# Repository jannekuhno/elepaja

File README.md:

# elepaja

#Setup
##1. Download KiCad
### Win:
http://kicad-pcb.org/ and install
### Linux:
sudo apt install kicad
##2. Clone repo
##3. Open project in KiCad
##4. Profit.

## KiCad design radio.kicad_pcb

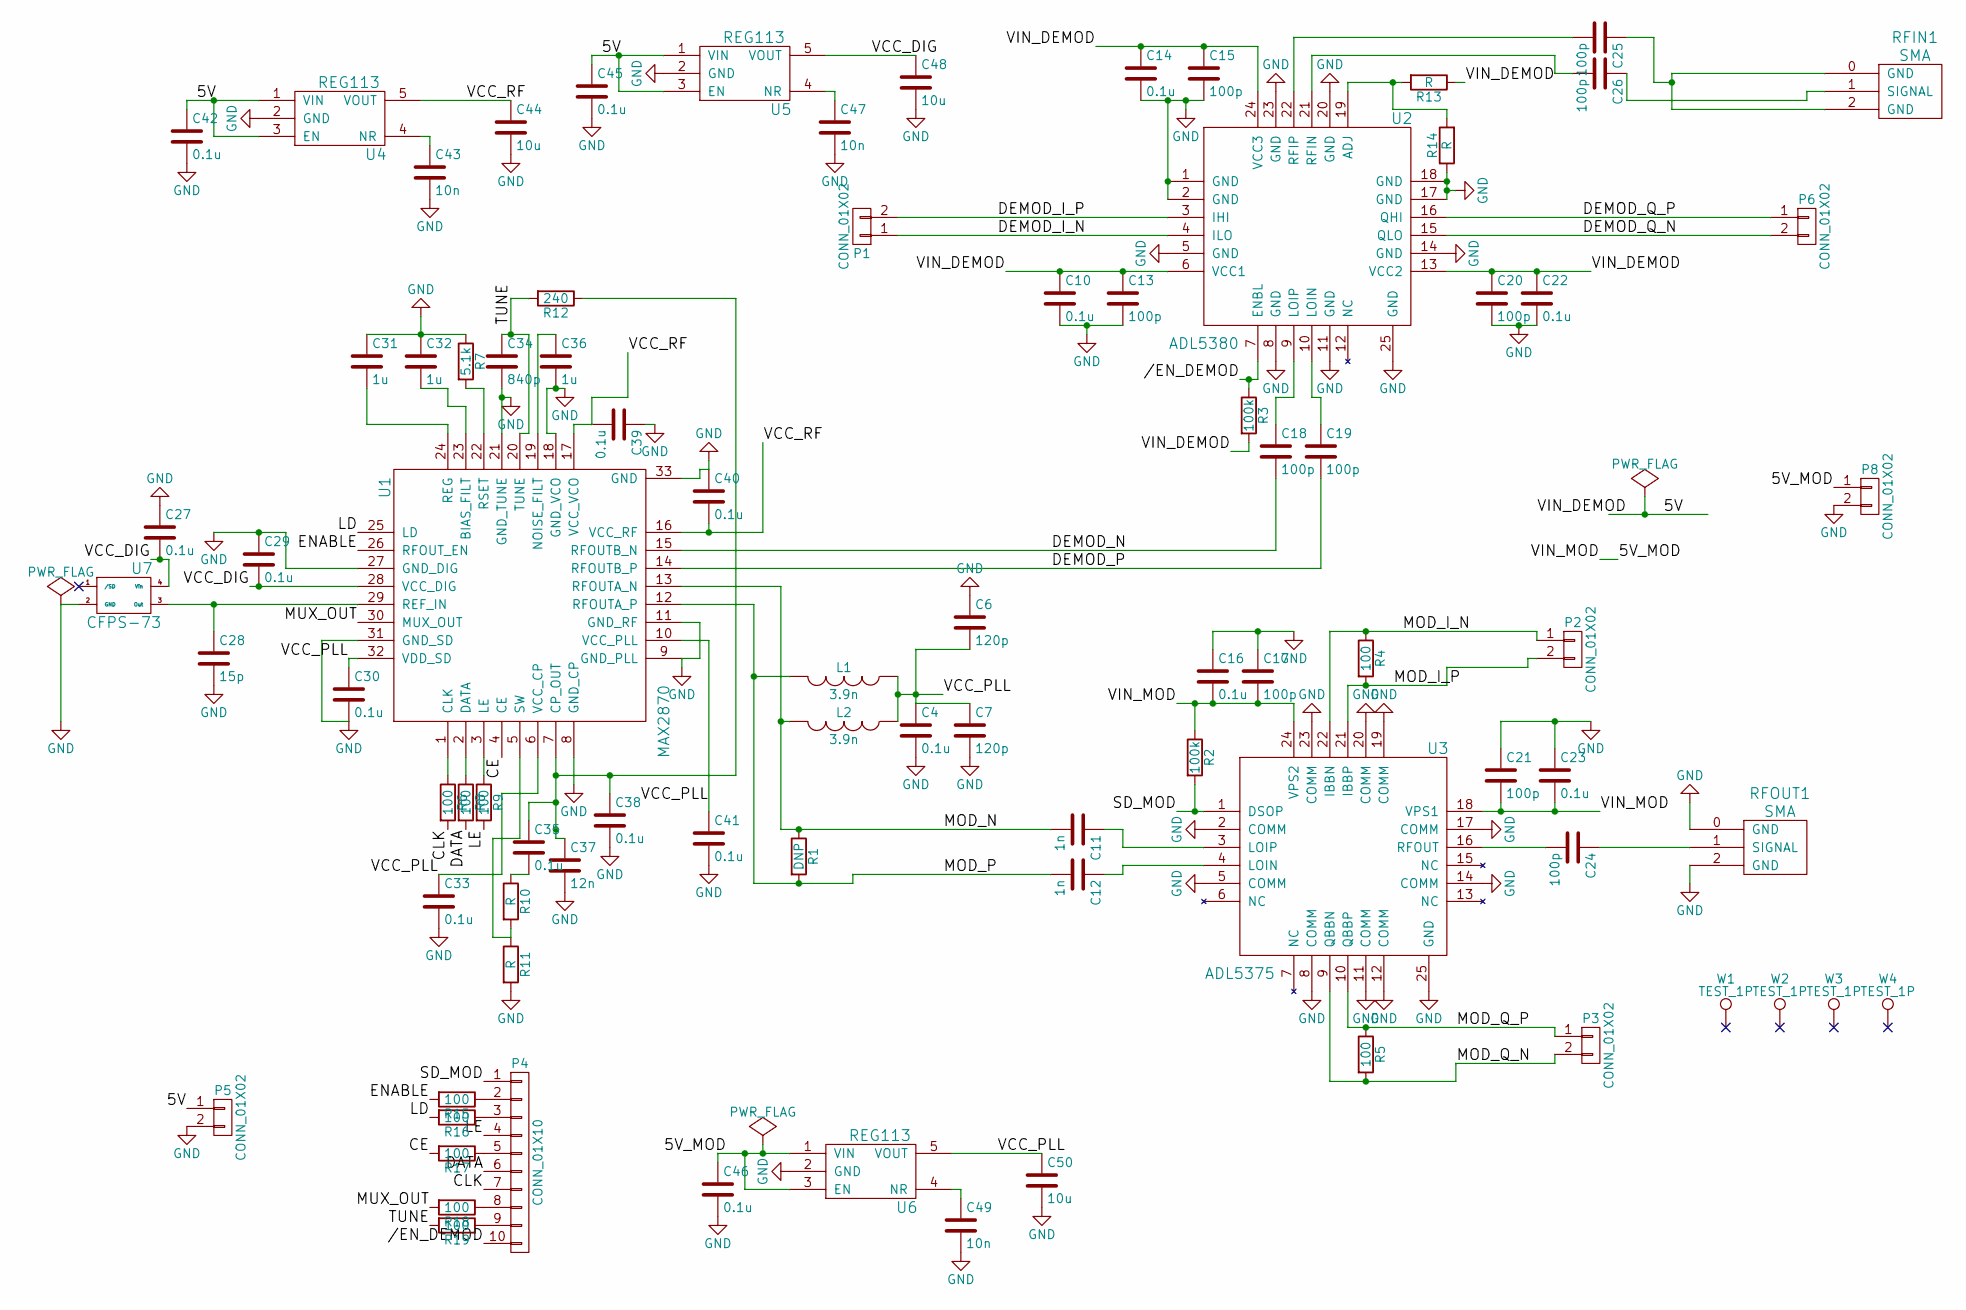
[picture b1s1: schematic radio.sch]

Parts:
C4, C10, C14, C16, C22, C23, C27, C29, C30, C33, C35, C38, C39, C40, C41, C42, C45, C46: 0.1u; C_0805
C6, C7: 120p; C_0805
C11, C12: 1n; C_0805
C13, C15, C17, C18, C19, C20, C21, C24, C25, C26: 100p; C_0805
C28: 15p; C_0805
C31, C32, C36: 1u; C_0805
C34: 840p; C_0805
C37: 12n; C_0805
C43, C47, C49: 10n; C_0805
C44, C48, C50: 10u; C_0805
L1, L2: 3.9n; C_0805
P1, P2, P3, P5, P6, P8: CONN_01X02; Pin_Header_Straight_1x02
P4: CONN_01X10; Pin_Header_Straight_1x10
R1: DNP; R_0805
R2, R3: 100k; R_0805
R4, R5, R6, R8, R9, R15, R16, R17, R18, R19: 100; R_0805
R7: 5.1k; R_0805
R10, R11, R13, R14: R; R_0805
R12: 240; R_0805
RFIN1: SMA; SMA_EDGE
RFOUT1: SMA; SMA_EDGE
U1: MAX2870; QFN-32-1EP_5x5mm_Pitch0.5mm
U2: ADL5380; QFN-24-1EP_4x4mm_Pitch0.5mm
U3: ADL5375; QFN-24-1EP_4x4mm_Pitch0.5mm
U4, U5, U6: REG113; SOT-23-5
U7: CFPS-73; OSC_7X5mm
W1, W2, W3, W4: TEST_1P; MountingHole_2.2mm_M2

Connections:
/5V: C10.1, C13.1, C14.1, C15.1, C20.1, C22.1, C42.1, C45.1, P5.1, R3.2, R13.1, U2.6 (VCC1), U2.13 (VCC2), U2.24 (VCC3), U4.1 (VIN), U4.3 (EN), U5.1 (VIN), U5.3 (EN)
/5V_MOD: C16.2, C17.2, C21.2, C23.2, C46.1, P8.1, R2.1, U3.18 (VPS1), U3.24 (VPS2), U6.1 (VIN), U6.3 (EN)
//EN_DEMOD: P4.10, R3.1, U2.7 (ENBL)
/CE: R17.2, U1.4 (CE)
/CLK: P4.7, R6.2
/DATA: P4.6, R8.2
/DEMOD_I_N: P1.1, U2.4 (ILO)
/DEMOD_I_P: P1.2, U2.3 (IHI)
/DEMOD_N: C18.2, U1.15 (RFOUTB_N)
/DEMOD_P: C19.2, U1.14 (RFOUTB_P)
/DEMOD_Q_N: P6.2, U2.15 (QLO)
/DEMOD_Q_P: P6.1, U2.16 (QHI)
/ENABLE: R15.2, U1.26 (RFOUT_EN)
/LD: R16.2, U1.25 (LD)
/LE: P4.4, R9.2
/MOD_I_N: P2.1, R4.1, U3.22 (IBBN)
/MOD_I_P: P2.2, R4.2, U3.21 (IBBP)
/MOD_N: C11.2, L2.2, R1.1, U1.13 (RFOUTA_N)
/MOD_P: C12.2, L1.2, R1.2, U1.12 (RFOUTA_P)
/MOD_Q_N: P3.2, R5.2, U3.9 (QBBN)
/MOD_Q_P: P3.1, R5.1, U3.10 (QBBP)
/MUX_OUT: R18.2, U1.30 (MUX_OUT)
/SD_MOD: P4.1, R2.2, U3.1 (DSOP)
/TUNE: C34.1, R12.2, R19.2, U1.20 (TUNE)
/VCC_DIG: C27.2, C29.2, C48.1, U1.28 (VCC_DIG), U5.5 (VOUT), U7.4 (Vin)
/VCC_PLL: C4.1, C6.2, C7.1, C30.1, C33.1, C41.1, C50.1, L1.1, L2.1, U1.6 (VCC_CP), U1.10 (VCC_PLL), U1.32 (VDD_SD), U6.5 (VOUT)
/VCC_RF: C39.2, C40.2, C44.1, U1.16 (VCC_RF), U1.17 (VCC_VCO), U4.5 (VOUT)
GND: C4.2, C6.1, C7.2, C10.2, C13.2, C14.2, C15.2, C16.1, C17.1, C20.2, C21.1, C22.2, C23.1, C27.1, C28.2, C29.1, C30.2, C31.1, C32.1, C33.2, C34.2, C36.2, C37.2, C38.2, C39.1, C40.1, C41.2, C42.2, C43.2, C44.2, C45.2, C46.2, C47.2, C48.2, C49.2, C50.2, P5.2, P8.2, R7.1, R11.2, R14.1, RFOUT1.0 (GND), RFOUT1.2 (GND), U1.8 (GND_CP), U1.9 (GND_PLL), U1.11 (GND_RF), U1.18 (GND_VCO), U1.21 (GND_TUNE), U1.27 (GND_DIG), U1.31 (GND_SD), U1.33 (GND), U2.1 (GND), U2.2 (GND), U2.5 (GND), U2.8 (GND), U2.11 (GND), U2.14 (GND), U2.17 (GND), U2.18 (GND), U2.20 (GND), U2.23 (GND), U2.25 (GND), U3.2 (COMM), U3.5 (COMM), U3.8 (COMM), U3.11 (COMM), U3.12 (COMM), U3.14 (COMM), U3.17 (COMM), U3.19 (COMM), U3.20 (COMM), U3.23 (COMM), U3.25 (GND), U4.2 (GND), U5.2 (GND), U6.2 (GND), U7.2 (GND)
unnamed: C11.1, U3.3 (LOIP)
unnamed: C12.1, U3.4 (LOIN)
unnamed: C18.1, U2.9 (LOIP)
unnamed: C19.1, U2.10 (LOIN)
unnamed: C24.1, RFOUT1.1 (SIGNAL)
unnamed: C24.2, U3.16 (RFOUT)
unnamed: C25.1, RFIN1.0 (GND), RFIN1.2 (GND)
unnamed: C25.2, U2.22 (RFIP)
unnamed: C26.1, RFIN1.1 (SIGNAL)
unnamed: C26.2, U2.21 (RFIN)
unnamed: C28.1, U1.29 (REF_IN), U7.3 (Out)
unnamed: C31.2, U1.24 (REG)
unnamed: C32.2, U1.23 (BIAS_FILT)
unnamed: C35.1, C37.1, C38.1, R12.1, U1.7 (CP_OUT)
unnamed: C35.2, R10.1
unnamed: C36.1, U1.19 (NOISE_FILT)
unnamed: C43.1, U4.4 (NR)
unnamed: C47.1, U5.4 (NR)
unnamed: C49.1, U6.4 (NR)
unnamed: P4.2, R15.1
unnamed: P4.3, R16.1
unnamed: P4.5, R17.1
unnamed: P4.8, R18.1
unnamed: P4.9, R19.1
unnamed: R6.1, U1.1 (CLK)
unnamed: R7.2, U1.22 (RSET)
unnamed: R8.1, U1.2 (DATA)
unnamed: R9.1, U1.3 (LE)
unnamed: R10.2, R11.1, U1.5 (SW)
unnamed: R13.2, R14.2, U2.19 (ADJ)

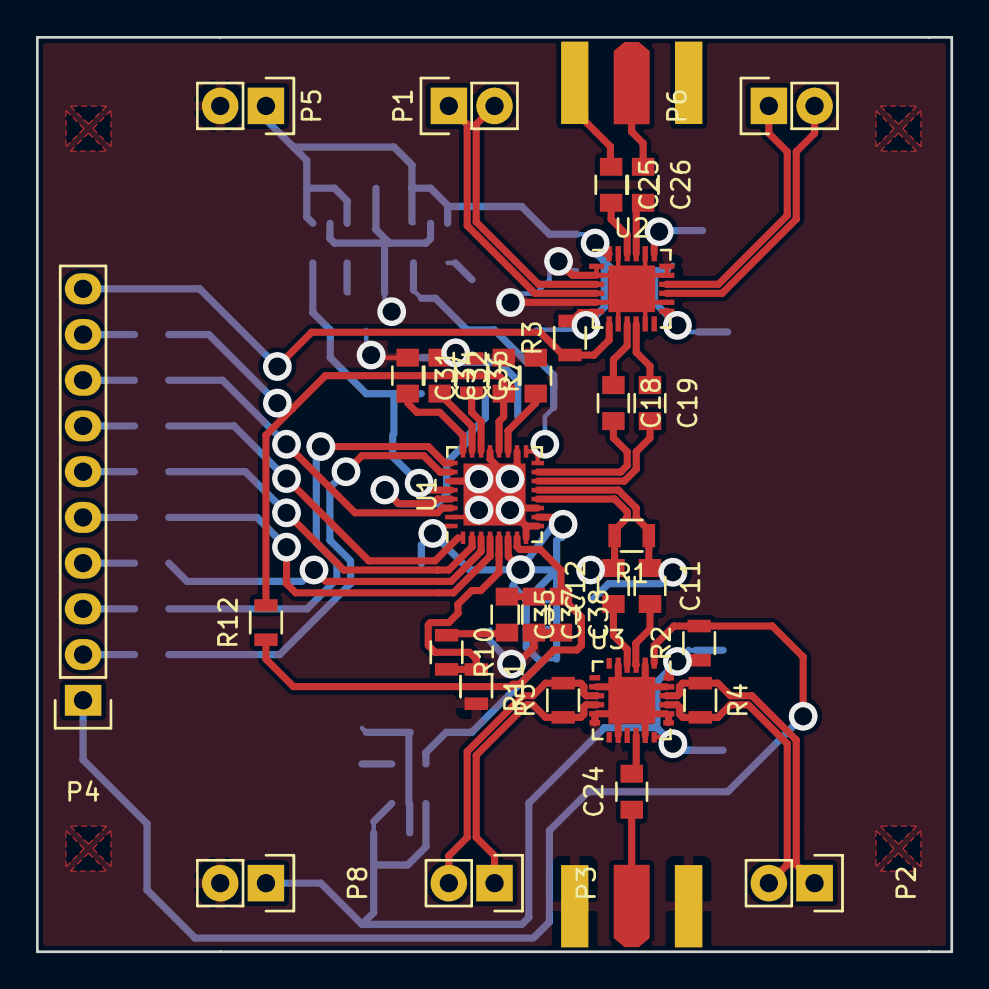
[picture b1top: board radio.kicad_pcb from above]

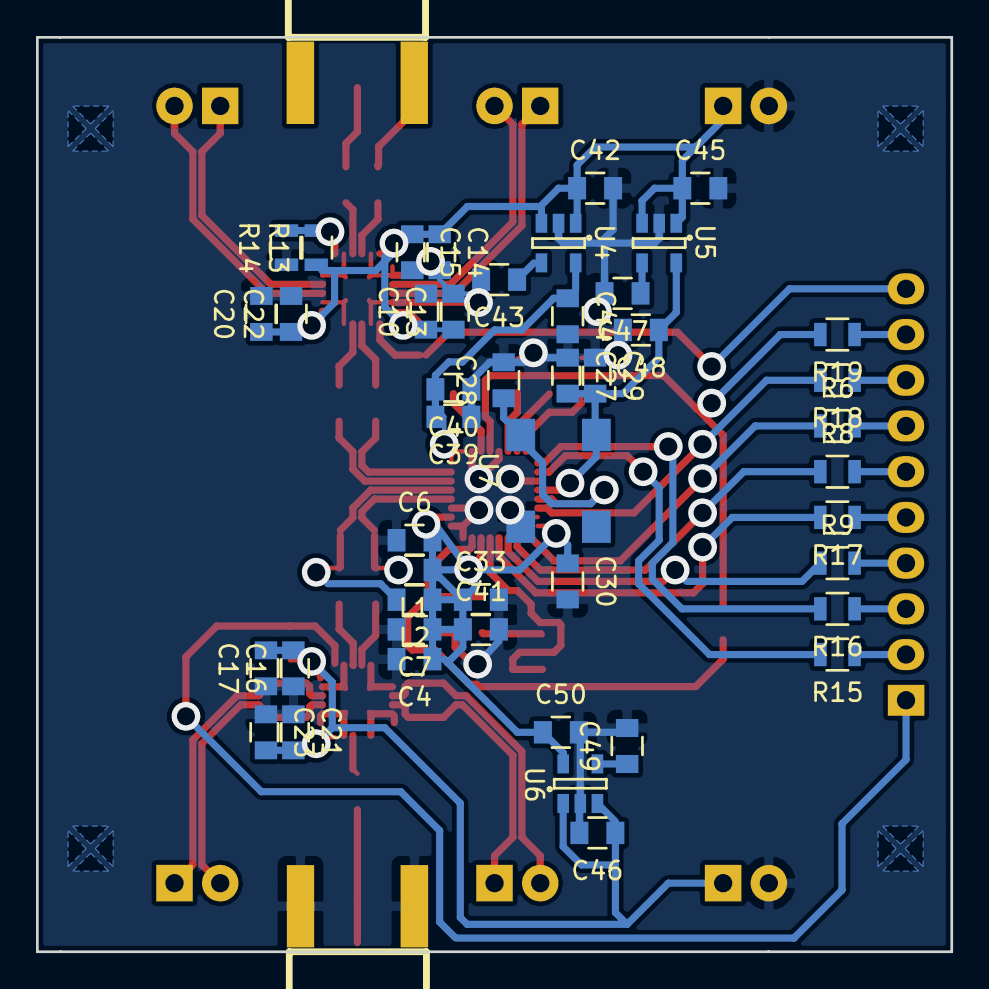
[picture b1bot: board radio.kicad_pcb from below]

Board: 2 copper layers, 50.8 x 50.8 mm, 81 parts (48 on the bottom side), 58 nets.

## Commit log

2016-12-03 Create elepaja repo
2016-12-03 remove backup and cache
2016-12-10 Values set up correctly
2016-12-10 Adjusted routes
2016-12-17 refactor git to store code as well
2016-12-17 Using 32-bit buffers instead of pointers due to the annoying way MAX2870 handles stuff
2016-12-17 Correct SPI setting
